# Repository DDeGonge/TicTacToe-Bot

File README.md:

# TicTacToe-Bot
Its a robot that plays tic tac toe.....

Build at your own risk, documentation is limited and the BOM below is NOT verified.

## BOM
* ~300g filament
* 4x 625 bearings
* 3x low profile gt2 20t 6mm drive pulleys
* 200mm gt2 closed loop belt
* 240mm gt2 closed loop belt
* 11x M3x6 SHCS (*BHCS probably better*) bolt. 4x more for the electronics box lid.
* 5x M3x16 SHCS bolts. Maybe get some M3x18 too just in case :D
* 1x M5x16 SHCS bolt
* 1x M5x40 SHCS bolt
* 2x M5 Nut
* 6x M3 Nut
* A few M3 and M5 washers
* some paper clips to connect servo to pen sleeve
* Uniball 60151 pen, or any other that are a similar size to fit in the sleeve.
* Some M2 bolt and nuts for raspberry pi camera mounting

* 2x nema 17 steppers, <=40mm length
* 1x mg90 servo
* Raspberry pi zero w
* Raspberry pi camera V1.X
* Adafruit Feather M4 or similar
* Stepper drivers, mine go one a custom pcb (files in repo) but you can solder your own or buy an OTS one
* MAX98357 I2S Audio Amplifier Module
* 8 ohm speaker

If you find any errors, please open an issue ticket!

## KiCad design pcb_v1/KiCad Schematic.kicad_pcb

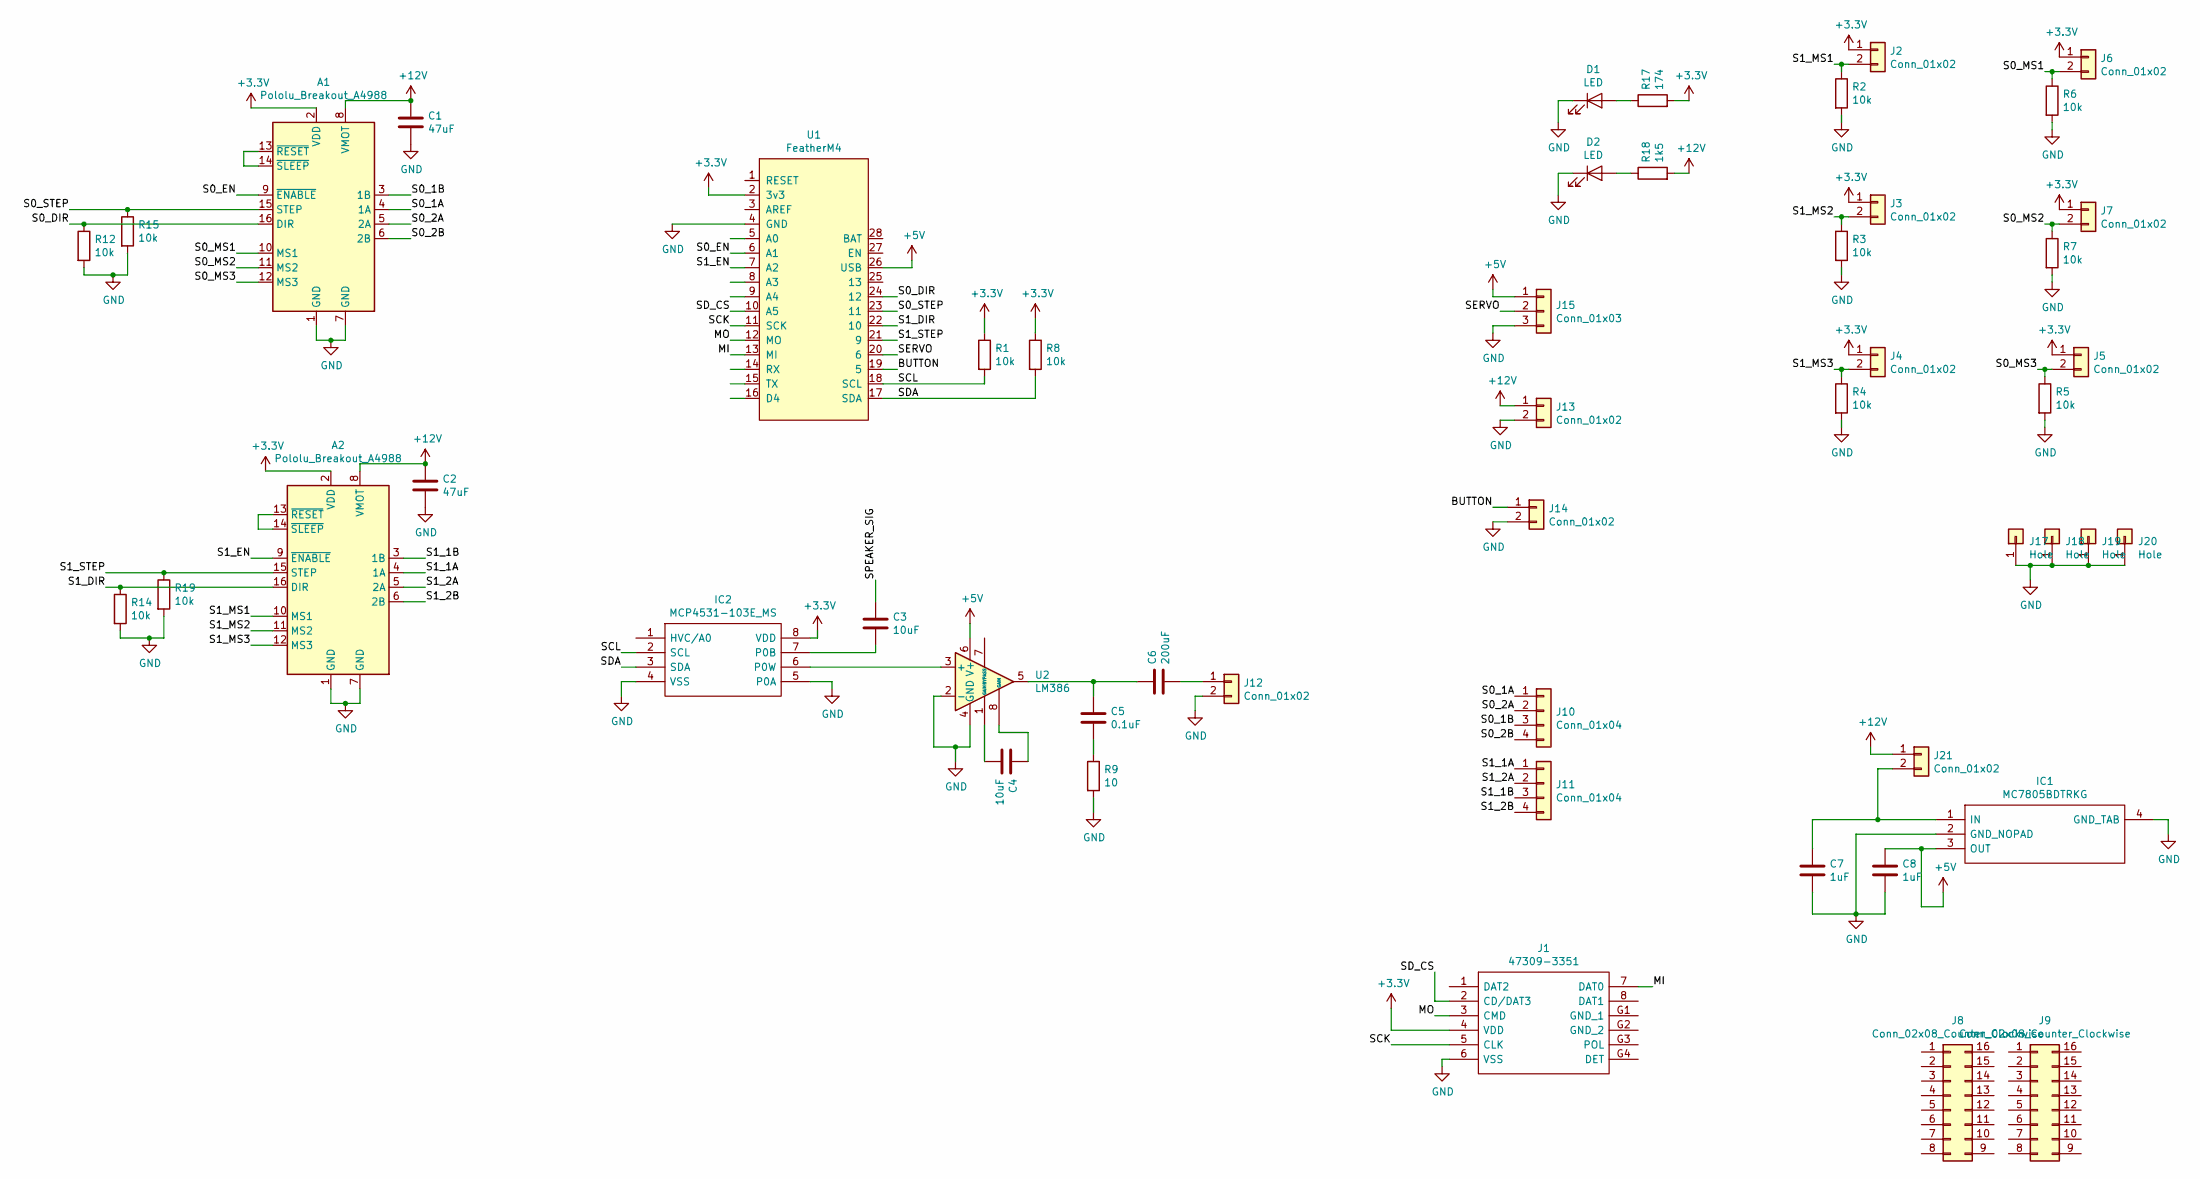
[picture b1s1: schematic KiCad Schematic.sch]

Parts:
A1, A2: Pololu_Breakout_A4988; Pololu_Breakout-16_15.2x20.3mm
C1, C2: 47uF; CP_Elec_6.3x5.8
C3, C4: 10uF; C_Radial_D5.0mm_H11.0mm_P2.00mm
C5: 0.1uF; C_0402_1005Metric
C6: 200uF; C_Radial_D6.3mm_H7.0mm_P2.50mm
C7, C8: 1uF; C_1206_3216Metric
D1, D2: LED; LED_0603_1608Metric
IC1: MC7805BDTRKG; TO229P990X238-4N; Mouser Part Number 863-MC7805BDTRKG
IC2: MCP4531-103E_MS; SOP65P490X110-8N; Mouser Part Number 579-MCP4531-103E/MS
J1: 47309-3351; 473093351; Mouser Part Number 538-47309-3351
J2, J3, J4, J5, J6, J7, J12, J14, J21: Conn_01x02; PinHeader_1x02_P2.54mm_Vertical
J8, J9: Conn_02x08_Counter_Clockwise; PinHeader_2x08_P2.54mm_Vertical
J10, J11: Conn_01x04; PinSocket_1x04_P2.54mm_Vertical
J13: Conn_01x02; BarrelJack_Wuerth_6941xx301002
J15: Conn_01x03; PinHeader_1x03_P2.54mm_Vertical
J17, J18, J19, J20: Hole; MountingHole_2.7mm_M2.5_DIN965_Pad
R1, R2, R3, R4, R5, R6, R7, R8, R12, R14, R15, R19: 10k; R_0603_1608Metric
R9: 10; R_0603_1608Metric
R17: 174; R_0603_1608Metric
R18: 1k5; R_0603_1608Metric
U1: FeatherM4; FeatherFootprint
U2: LM386; SOIC-8_3.9x4.9mm_P1.27mm

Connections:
+3V3: A1.2 (VDD), A2.2 (VDD), IC2.8 (VDD), J1.4 (VDD), J2.1, J3.1, J4.1, J5.1, J6.1, J7.1, R1.1, R8.1, R17.2, U1.2 (3v3)
+5V: C8.1, IC1.3 (OUT), J15.1, U1.26 (USB), U2.6 (V+)
+12V: A1.8 (VMOT), A2.8 (VMOT), C1.1, C2.1, J13.1, J21.1, R18.2
/BUTTON: J14.1, U1.19 (5)
/MI: J1.7 (DAT0), U1.13 (MI)
/MO: J1.3 (CMD), U1.12 (MO)
/S0_1A: A1.4 (1A), J10.1
/S0_1B: A1.3 (1B), J10.3
/S0_2A: A1.5 (2A), J10.2
/S0_2B: A1.6 (2B), J10.4
/S0_DIR: A1.16 (DIR), R12.1, U1.24 (12)
/S0_EN: A1.9 (~ENABLE), U1.6 (A1)
/S0_MS1: A1.10 (MS1), J6.2, R6.1
/S0_MS2: A1.11 (MS2), J7.2, R7.1
/S0_MS3: A1.12 (MS3), J5.2, R5.1
/S0_STEP: A1.15 (STEP), R15.1, U1.23 (11)
/S1_1A: A2.4 (1A), J11.1
/S1_1B: A2.3 (1B), J11.3
/S1_2A: A2.5 (2A), J11.2
/S1_2B: A2.6 (2B), J11.4
/S1_DIR: A2.16 (DIR), R14.1, U1.22 (10)
/S1_EN: A2.9 (~ENABLE), U1.7 (A2)
/S1_MS1: A2.10 (MS1), J2.2, R2.1
/S1_MS2: A2.11 (MS2), J3.2, R3.1
/S1_MS3: A2.12 (MS3), J4.2, R4.1
/S1_STEP: A2.15 (STEP), R19.1, U1.21 (9)
/SCK: J1.5 (CLK), U1.11 (SCK)
/SCL: IC2.2 (SCL), R1.2, U1.18 (SCL)
/SDA: IC2.3 (SDA), R8.2, U1.17 (SDA)
/SD_CS: J1.2 (CD/DAT3), U1.10 (A5)
/SERVO: J15.2, U1.20 (6)
/SPEAKER_SIG: C3.1
GND: A1.1 (GND), A1.7 (GND), A2.1 (GND), A2.7 (GND), C1.2, C2.2, C7.2, C8.2, D1.1 (K), D2.1 (K), IC1.2 (GND_NOPAD), IC1.4 (GND_TAB), IC2.4 (VSS), IC2.5 (P0A), J1.6 (VSS), J12.2, J13.2, J14.2, J15.3, J17.1, J18.1, J19.1, J20.1, R2.2, R3.2, R4.2, R5.2, R6.2, R7.2, R9.2, R12.2, R14.2, R15.2, R19.2, U1.4 (GND), U2.2 (-), U2.4 (GND)
unnamed: A1.13 (~RESET), A1.14 (~SLEEP)
unnamed: A2.13 (~RESET), A2.14 (~SLEEP)
unnamed: C3.2, IC2.7 (P0B)
unnamed: C4.1, U2.8 (GAIN)
unnamed: C4.2, U2.1 (GAIN)
unnamed: C5.1, C6.1, U2.5
unnamed: C5.2, R9.1
unnamed: C6.2, J12.1
unnamed: C7.1, IC1.1 (IN), J21.2
unnamed: D1.2 (A), R17.1
unnamed: D2.2 (A), R18.1
unnamed: IC2.6 (P0W), U2.3 (+)

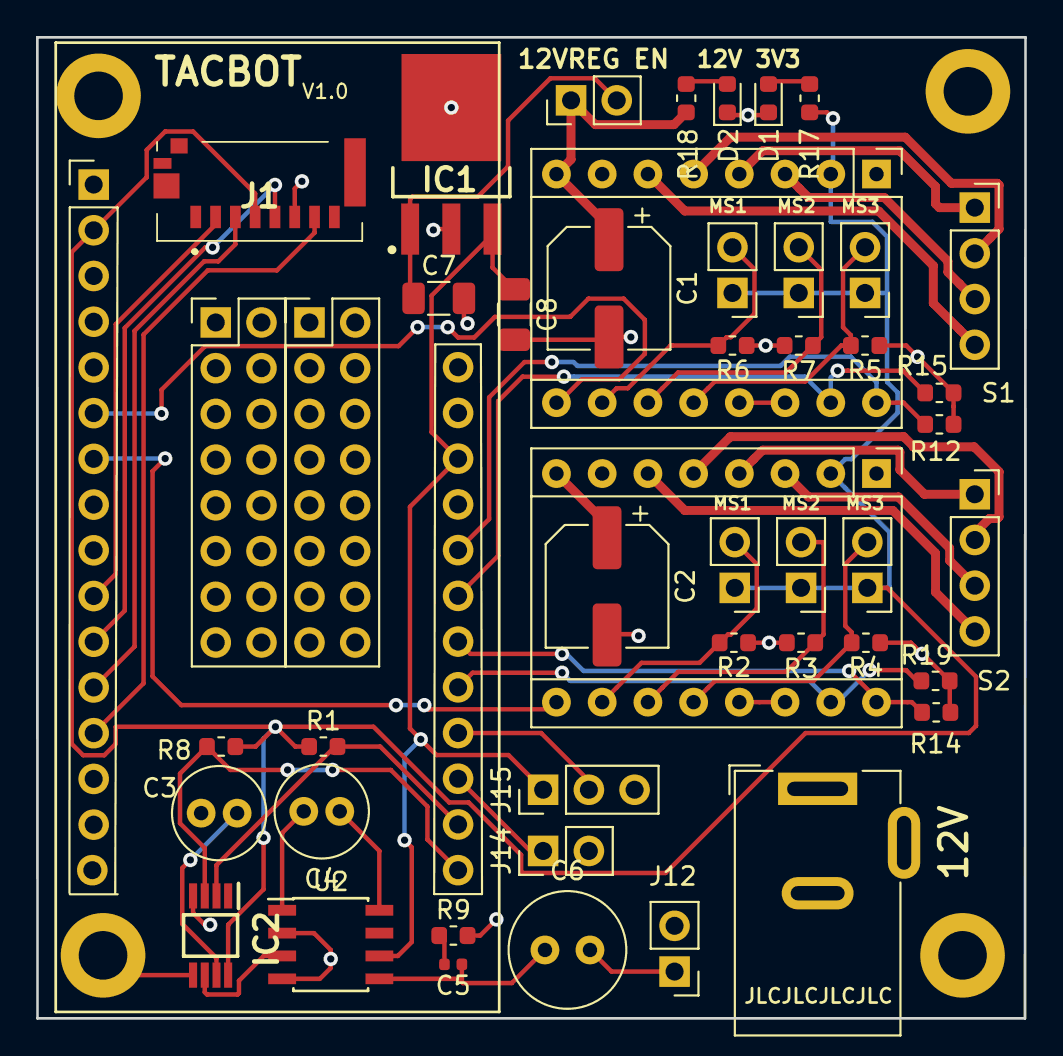
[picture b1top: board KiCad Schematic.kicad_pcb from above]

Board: 2 copper layers, 54.9 x 54.5 mm, 51 parts (0 on the bottom side), 44 nets.

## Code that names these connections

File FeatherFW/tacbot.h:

#include "funks.h"

#define s0_en A1
#define s0_step 11
#define s0_dir 12
#define s1_en A2
#define s1_step 9
#define s1_dir 10
#define servo_pin 4

// #define servo_pin 6
// #define button_in 5


Adafruit_NeoPixel pixel = Adafruit_NeoPixel(1, 8, NEO_GRB + NEO_KHZ800);

using namespace std;

struct stepper
{
  public:
  void init(int s_pin, int d_pin, int e_pin, bool reverse);
  void enable();
  void disable();
  void set_dir(bool dir);
  bool step_if_needed();
  void take_step();
  void overwrite_pos(int32_t newpos);
  void update_config(int32_t steps_per_rev_new);
  void set_rad_target(double target);
  void set_zero_rads(double rads);
  int32_t get_steps();
  float get_rads();

  private:
  bool current_dir = false;
  int step_pin;
  int dir_pin;
  int en_pin;
  int reverse;
  double target_rads = 0;
  int32_t step_count = 0;
  float steps_per_rev = 3200;
};

struct scara_bot
{
  public:
  void init(stepper step0, stepper step1, Servo servo_obj);
  void configure(float arm0_mm_new, float arm1_mm_new, float s0_spr_new, float s1_spr_new, float x0_off_new, float y0_off_new, float pen_new_up, float pen_new_dn);
  void enable_motors(bool x, bool y);
  void disable_motors(bool x, bool y);
  void zero(float x_target_mm, float y_target_mm);
  void move_motor_linear(float x_target_mm, float y_target_mm, float v_max);
  void move_motor_arc(float x_target_mm, float y_target_mm, float ival, float jval, float v_max, bool cw);
  void set_def_speeds(float new_accel, float new_vel);
  void get_pos(float &xpos_mm, float &ypos_mm);
  void set_pos_mode(bool abs_true);
  void lower_pen();
  void raise_pen();

  void debug_print();

  private:
  double cos_solve(float l1, float l2, float l3);
  void ik_solve(float xtar_mm, float ytar_mm, float &theta0, float &theta1);

  stepper s0;
  stepper s1;
  Servo p_servo;

  bool absmode = true;
  float xpos_mm = 0;
  float ypos_mm = 0;
  float def_accel = 500;
  float def_vel = 100;
  float arm0_mm = 100.5;
  float arm1_mm = 90;
  float x0_offset_mm = 25;
  float y0_offset_mm = 135;
  float servo_up_pwm = 0;
  float servo_dn_pwm = 0;
};

struct gcode_command_floats
{
  gcode_command_floats(vector<string> inputs);

  public:
  float fetch(char com_key);
  bool com_exists(char com_key);
  

  private:
  void parse_float(string inpt, char &cmd, float &value);

  vector<char> commands;
  vector<float> values;
};

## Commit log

2020-08-23 update cam driver and test script
2020-08-23 bugfix
2020-08-23 add image rotation
2020-08-23 change rotation type
2020-08-23 ffs fine back to what I was doing
2020-08-23 stuffs yes
2020-08-23 debugging stuffs
2020-08-23 bugfixes dimension issue
2020-08-23 bugfixes, finish initial game loop, stuff
2020-08-23 many updates and fixes
2020-08-23 update feather fw plus other stuff
2020-08-24 cad updates, feather fw improvements
2020-08-28 cad updates for accuracy, add audio support to firmware, config updates
2020-08-30 cad improvements, firmware bugfixes, more python stuff. Gimme a break I cant keep track of all this
2020-08-30 bugfixes
2020-08-30 update test function
2020-08-30 add auto-gen bot first move
2020-08-31 missing paranthesis
2020-08-31 squishin the buggies
2020-08-31 add win line draw thing
2020-08-31 fix config
2020-09-01 add butterfly for fun
2020-09-01 bugfixes and maybe fix axis issue with AI
2020-09-01 make it better
2020-09-02 fixing stuff and add swatting
2020-09-05 add audio and audio driver, minor cad tweaks
2020-09-05 rename audio files
2020-09-05 add ebox cad and integrate speaker into routine
2020-09-05 add extra audio stuffs
2020-09-05 remove dumb pycache
2020-09-05 optimize
2020-09-05 bugfixes?
2020-09-05 stuffffff!
2020-09-05 bugfixes for the swatting
2020-09-05 routine improvements
2020-09-05 improve swatting, now testing distract
2020-09-05 almost done!
2020-09-05 cleanup for release
2020-09-05 draw slower, add park at end of game
2020-09-05 optimizations
2020-09-06 add electronics box cad and park optimizationz
2020-09-06 move speaker stuff to config
2020-09-06 forgot these
2020-09-07 CAT MODE
2020-09-09 video stuff
2020-09-09 i am poet bot
2020-09-12 add pic dumps for youtube stuff
2020-09-13 stuff for memes
2020-09-13 more memes
2020-09-18 cleanup
